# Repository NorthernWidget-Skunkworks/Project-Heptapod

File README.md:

# Project Ophiura

*I2C and RS-485 bus breakout boards by [Northern Widget LLC](https://www.northernwidget.com)*

## Namesake

***Ophiura albida*, a brittle star.** *Photo by Andrea Bonifazi, [CC BY-SA 4.0](https://creativecommons.org/licenses/by-sa/4.0/).*

*Ophiura* (pronounced "oh-FYOO-rah"; from Greek *ophioura*, "snake-tailed") is a genus of brittle stars — marine invertebrates related to sea stars but built for sensing and coordinated movement. When a brittle star locomotes, one arm leads as a sensory probe while the other four row in coordinated response. Crucially, all four trailing arms continuously send proprioceptive feedback back to the central disc, which integrates and adjusts. The result is a true bidirectional hub: signals flow outward from one to four, and inward from four back to one.

This maps directly onto I2C: one upstream connection carries clock and commands outward to sensors, while sensors pull the data line back to return their readings. Project Ophiura is not a splitter — it is a hub.

## Overview

Project Ophiura is a family of compact breakout boards for distributing bus connections. The most widely used board is the **BusBreakout\_I2C**, which connects a single upstream I2C connection (SCL, SDA, VCC, GND) to four independent downstream screw-terminal ports — making it easy to wire multiple sensors to one data logger or microcontroller without soldering.

Because the board is simply a passive connection hub, it can also serve as a general-purpose wire distribution point for any four-wire signal.

## [BusBreakout\_I2C](BusBreakout_I2C/)

One upstream I2C connection (typically a 4-pin header from a data logger such as the [Northern Widget Margay](https://github.com/NorthernWidget/Project-Margay)) fans out to four downstream screw-terminal ports. Each port carries SCL, SDA, VCC, and GND. No active components — plug in, tighten screws, done.

### Pinout

| Pin | Signal | Description |
|-----|--------|-------------|
| 1 | SCL | I2C clock |
| 2 | SDA | I2C data |
| 3 | 3V3 | 3.3 V power |
| 4 | GND | Ground |

Connectors are 4-position, 2.54 mm pitch screw terminals (OnShore OSTVN04A150, Digikey [ED10563-ND](https://www.digikey.com/en/products/detail/on-shore-technology-inc/OSTVN04A150/1588866)).

### [BusBreakout\_I2C\_Mini](BusBreakout_I2C_Mini/)

Electrically identical to the BusBreakout\_I2C but in a smaller footprint for space-constrained installations. Mounting holes are unpopulated (DNP) on this variant.

## [Switched\_I2C](Switched_I2C/)

Active I2C breakout with per-port hardware isolation and switchable power. Unlike the passive BusBreakout\_I2C, this board connects only one downstream port's SDA line to the master at a time — allowing **multiple sensors with the same I2C address** to share a single bus without address conflicts.

### Key components

| Component | Function |
|-----------|----------|
| TCA9534A (I2C GPIO expander) | Controls mux select lines and power switches over I2C |
| SN74LV4051A (8-channel analog mux) | Hardware-isolates SDA per port |
| N-channel MOSFETs | Switch VCC to each downstream port independently |

### How it works

The **TCA9534A** (I2C address 0x20–0x27, configurable via A0/A1/A2 pins) drives GPIO outputs that:

1. Set the SN74LV4051A select lines to route one port's SDA to the master
2. Drive MOSFETs to power individual ports on or off

SCL is shared across all ports. Only the selected port's SDA is connected to the bus — the others are hardware-isolated. This means four identical sensors (same chip, same I2C address) can be connected to four ports and addressed one at a time by switching the mux. A `/INT` interrupt output from the TCA9534A can signal the host when a port state changes.

## [RS485\_Breakout](RS485_Breakout/)

Passive RS-485 bus breakout providing screw-terminal access to a full-duplex RS-485 differential pair plus power. No transceiver on board — the RS-485 driver/receiver is expected on the data logger or microcontroller side.

### Pinout

| Pin | Signal | Description |
|-----|--------|-------------|
| 1 | VCC | Power |
| 2 | GND | Ground |
| 3 | TX+ | Transmit positive (from master) |
| 4 | TX− | Transmit negative (from master) |
| 5 | RX+ | Receive positive (to master) |
| 6 | RX− | Receive negative (to master) |

Connectors are 6-position, 2.54 mm pitch screw terminals (OnShore OSTVN06A150, Digikey [ED10565-ND](https://www.digikey.com/en/products/detail/on-shore-technology-inc/OSTVN06A150/1588868)).

### Termination

SMT normally-open jumpers are provided for line termination. Close the jumper if this board is at the physical end of the RS-485 bus (standard termination: 120 Ω across the differential pair). Four mounting holes are provided in two sizes: 2×56 and 4×40.

## License

<br />This work is licensed under a <a rel="license" href="http://creativecommons.org/licenses/by-sa/4.0/">Creative Commons Attribution-ShareAlike 4.0 International License</a>.

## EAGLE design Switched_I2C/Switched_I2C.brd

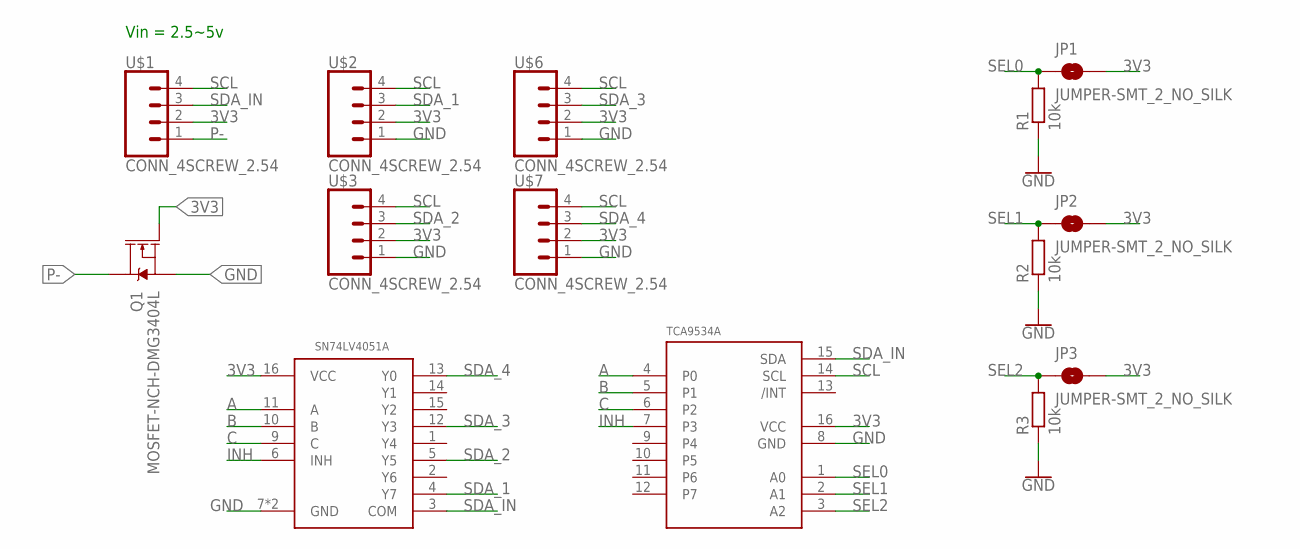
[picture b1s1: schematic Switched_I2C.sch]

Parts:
JP1, JP2, JP3: JUMPER-SMT_2_NO_SILK; SMT-JUMPER_2_NO_SILK
Q1: MOSFET-NCH-DMG3404L; SOT23-3
R1, R2, R3: 10k; R0603
U$1, U$2, U$3, U$6, U$7: CONN_4SCREW_2.54; 1X04
U$5: SN74LV4051ATSSOP; TSSOP16
U$8: TCA9534A; TSSOP16

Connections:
3V3: JP1.2, JP2.2, JP3.2, Q1.1 (G), U$1.2, U$2.2, U$3.2, U$5.16 (VCC), U$6.2, U$7.2, U$8.16 (VCC)
A: U$5.11 (A), U$8.4 (P0)
B: U$5.10 (B), U$8.5 (P1)
C: U$5.9 (C), U$8.6 (P2)
GND: Q1.2 (S), R1.1, R2.1, R3.1, U$2.1, U$3.1, U$5.7 (GND), U$5.8 (GND), U$6.1, U$7.1, U$8.8 (GND)
INH: U$5.6 (INH), U$8.7 (P3)
P-: Q1.3 (D), U$1.1
SCL: U$1.4, U$2.4, U$3.4, U$6.4, U$7.4, U$8.14 (SCL)
SDA_1: U$2.3, U$5.4 (Y7)
SDA_2: U$3.3, U$5.5 (Y5)
SDA_3: U$5.12 (Y3), U$6.3
SDA_4: U$5.13 (Y0), U$7.3
SDA_IN: U$1.3, U$5.3 (COM), U$8.15 (SDA)
SEL0: JP1.1, R1.2, U$8.1 (A0)
SEL1: JP2.1, R2.2, U$8.2 (A1)
SEL2: JP3.1, R3.2, U$8.3 (A2)

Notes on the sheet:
Vin = 2.5~5v

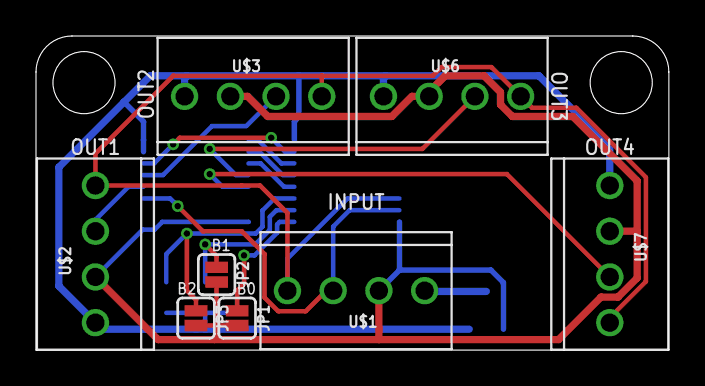
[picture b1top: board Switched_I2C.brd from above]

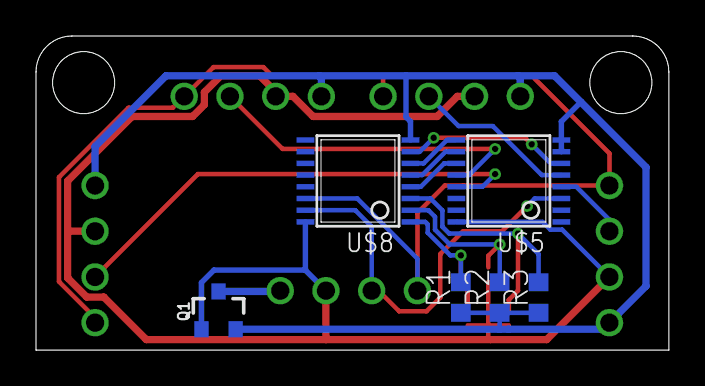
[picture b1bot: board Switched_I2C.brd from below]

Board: 2 copper layers, 35.2 x 17.4 mm, 15 parts (7 on the bottom side), 16 nets.

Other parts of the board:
U$9: NWLOGO_SMALL

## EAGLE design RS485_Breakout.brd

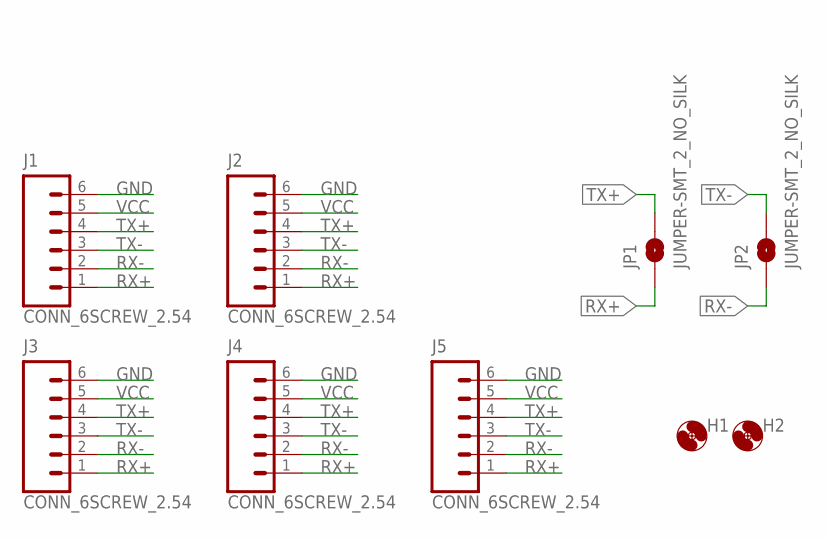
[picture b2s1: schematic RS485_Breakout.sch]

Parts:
H1, H2: MOUNTING_HOLE4_NP; 4_40
J1, J2, J3, J4, J5: CONN_6SCREW_2.54; 1X06_SCREW
JP1, JP2: JUMPER-SMT_2_NO_SILK; SMT-JUMPER_2_NO_SILK

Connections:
GND: J1.6, J2.6, J3.6, J4.6, J5.6
RX+: J1.1, J2.1, J3.1, J4.1, J5.1, JP1.1
RX-: J1.2, J2.2, J3.2, J4.2, J5.2, JP2.1
TX+: J1.4, J2.4, J3.4, J4.4, J5.4, JP1.2
TX-: J1.3, J2.3, J3.3, J4.3, J5.3, JP2.2
VCC: J1.5, J2.5, J3.5, J4.5, J5.5

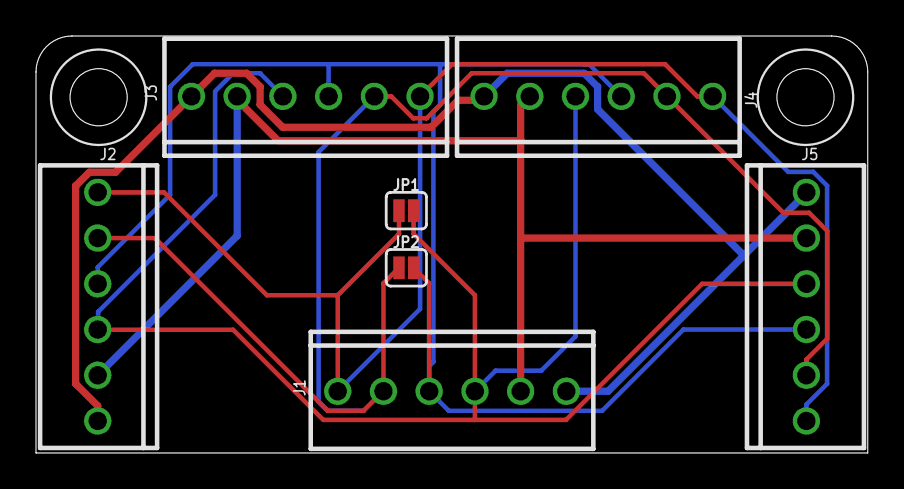
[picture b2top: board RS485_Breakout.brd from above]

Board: 2 copper layers, 46.2 x 23.2 mm, 10 parts (1 on the bottom side), 6 nets.

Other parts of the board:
U$1: NWLOGO_MED

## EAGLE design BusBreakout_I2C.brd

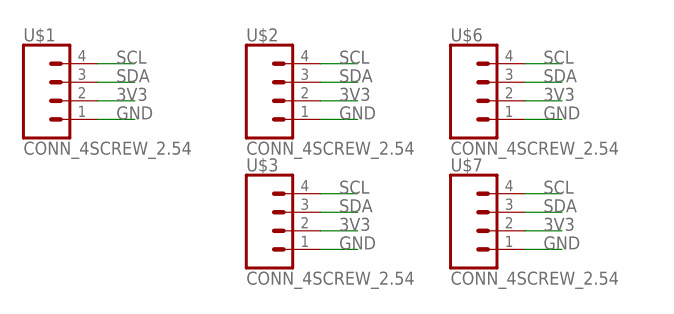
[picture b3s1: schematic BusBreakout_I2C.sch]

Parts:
U$1, U$2, U$3, U$6, U$7: CONN_4SCREW_2.54; 1X04

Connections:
3V3: U$1.2, U$2.2, U$3.2, U$6.2, U$7.2
GND: U$1.1, U$2.1, U$3.1, U$6.1, U$7.1
SCL: U$1.4, U$2.4, U$3.4, U$6.4, U$7.4
SDA: U$1.3, U$2.3, U$3.3, U$6.3, U$7.3

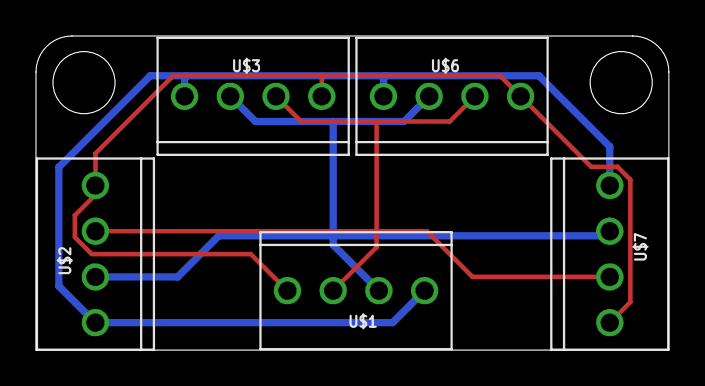
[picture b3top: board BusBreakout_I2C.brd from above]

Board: 2 copper layers, 35.2 x 17.4 mm, 6 parts (1 on the bottom side), 4 nets.

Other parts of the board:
U$4: NWLOGO_MED

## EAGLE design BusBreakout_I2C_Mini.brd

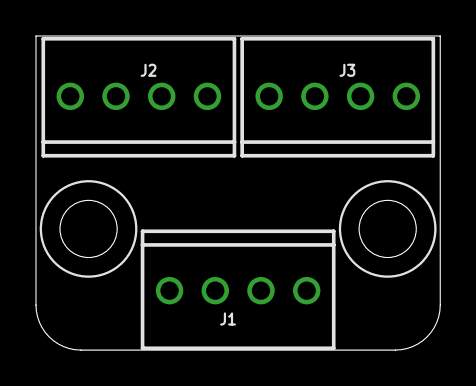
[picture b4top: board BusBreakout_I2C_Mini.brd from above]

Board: 2 copper layers, 22.5 x 17.4 mm, 5 parts (0 on the bottom side), 4 nets, no tracks yet.

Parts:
H1, H2: 4_40
J1, J2, J3: CONN_42.54_SCREW; 1X04_SCREW

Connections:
3V3: J1.2, J2.2, J3.2
GND: J1.1, J2.1, J3.1
SCL: J1.4, J2.4, J3.4
SDA: J1.3, J2.3, J3.3

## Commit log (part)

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2018-03-02 Inital commit with I2C board
2018-03-03 Finished layout and generated gerbers
2018-03-06 Added switched I2C board
    Initial layout complete, silkscreen cleanup needed before review
2018-03-06 Fixed silk screen issues on Switched_I2C board
2018-10-19 Added RS485 Heptapod
    Added RS485 heptapod for use with TP-Downhole Longbow, ready for review before sending out. Also added gerbers for switched and conventional heptapod. Evidently been sitting in buffer for 6 months. O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
2018-10-27 Generated Gerbers for RS-485 Breakout
    Generated new gerbers for RS-485 breakout, also regenerated gerbers for I2C breakout, OSH Park had issues with existing zip file
2018-12-18 CC-BY-SA
2020-08-12 Added mini breakout board
2022-09-28 Schulz 2020
2022-09-28 Zenodo DOI badge

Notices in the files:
parts and their libraries:
SparkFun-Jumpers: Licensing: Creative Commons ShareAlike 4.0 International - https://creativecommons.org/licenses/by-sa/4.0
